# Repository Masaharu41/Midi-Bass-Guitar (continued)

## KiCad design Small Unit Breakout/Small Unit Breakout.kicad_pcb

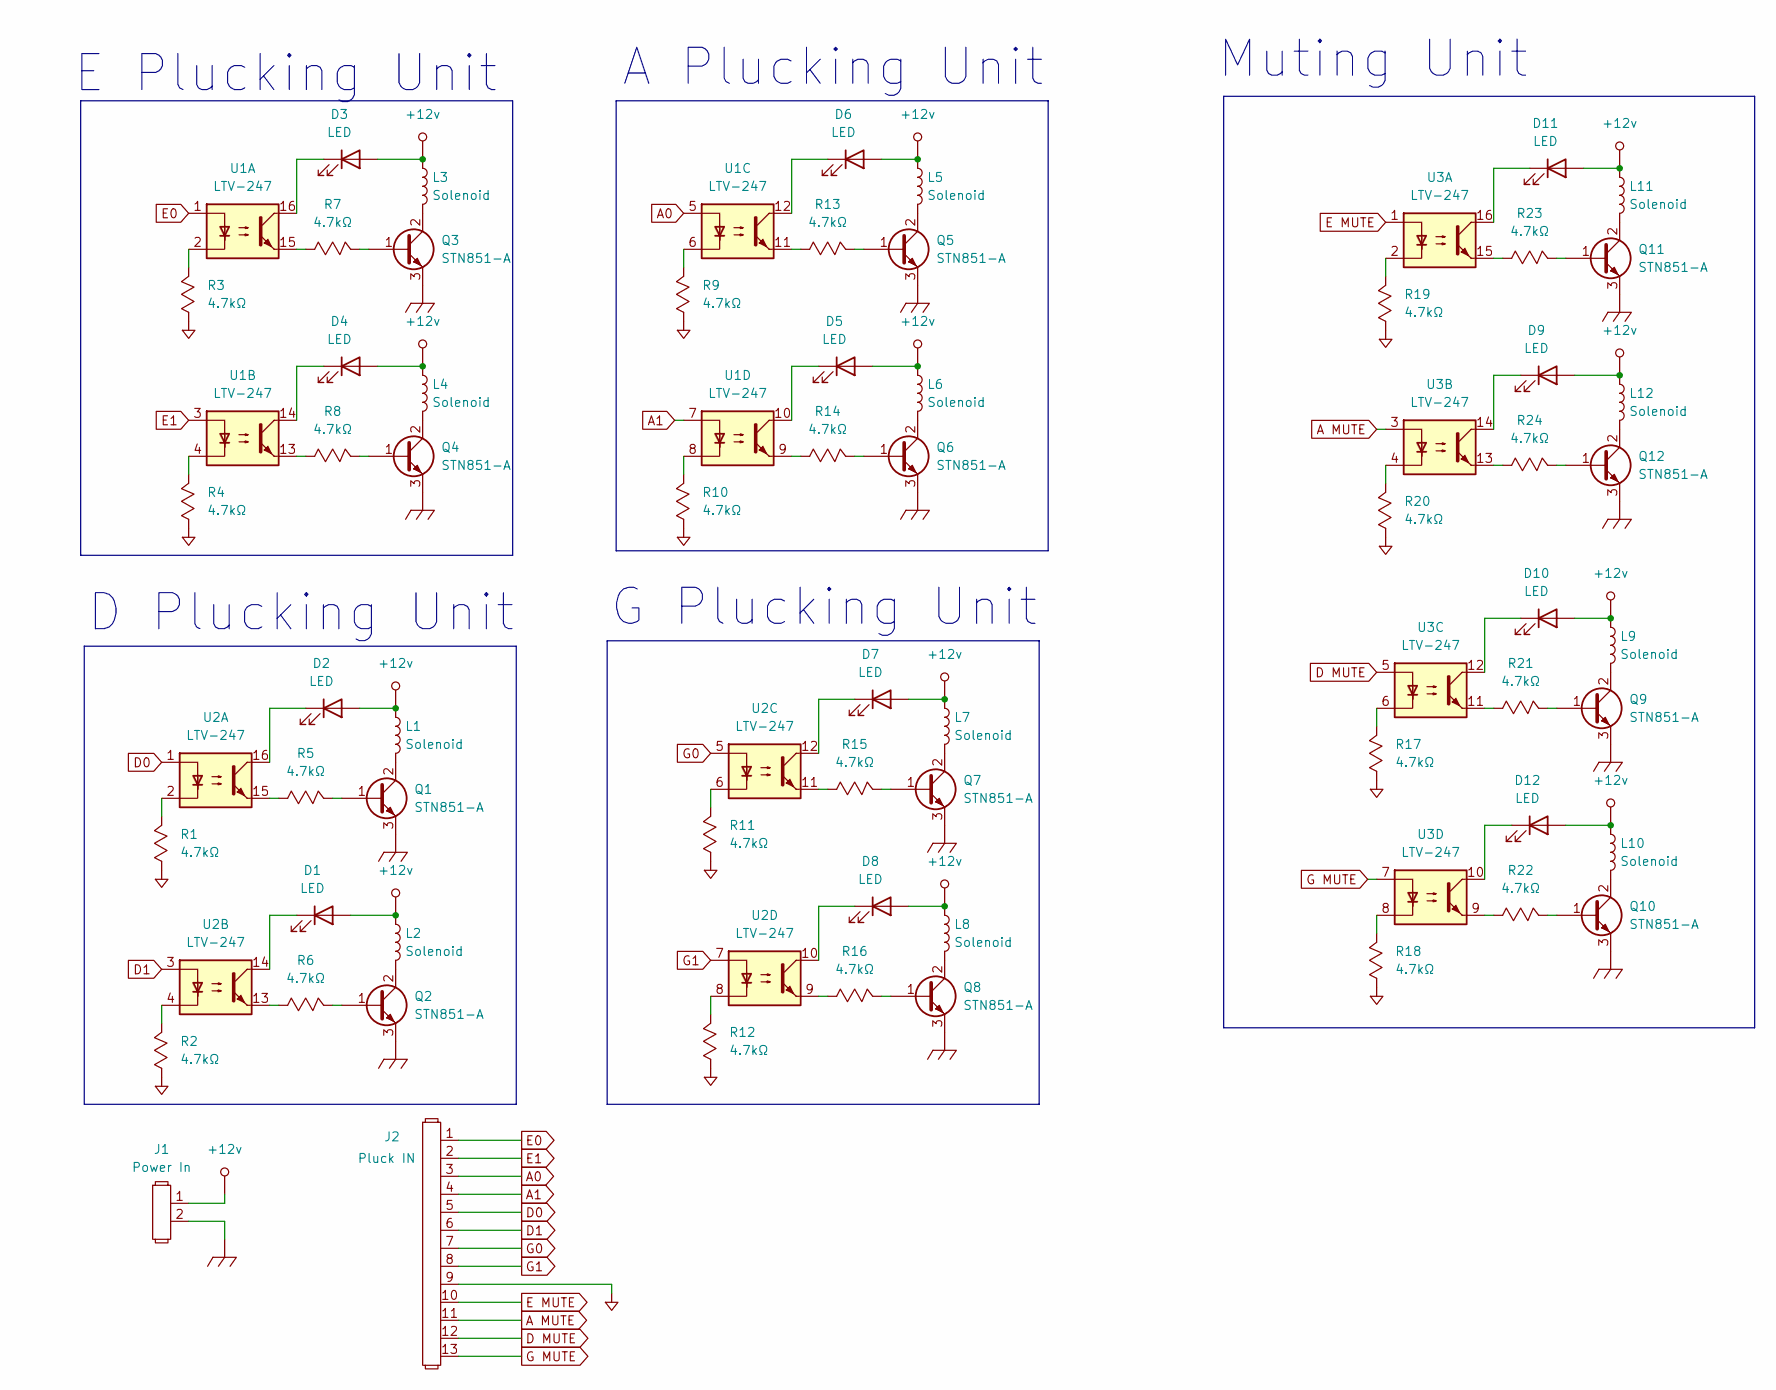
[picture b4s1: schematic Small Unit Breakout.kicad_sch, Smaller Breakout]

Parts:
D1, D2, D3, D4, D5, D6, D7, D8, D9, D10, D11, D12: LED; LED_0805_2012Metric_Pad1.15x1.40mm_HandSolder
J1: Power In; Two_Pin_Screw_Terminal
J2: Pluck IN; PinHeader_1x13_P2.54mm_Vertical
L1, L2, L3, L4, L5, L6, L7, L8, L9, L10, L11, L12: Solenoid; PinHeader_1x02_P2.54mm_Vertical
Q1, Q2, Q3, Q4, Q5, Q6, Q7, Q8, Q9, Q10, Q11, Q12: STN851-A; SOT-223-3_TabPin2
R1, R2, R3, R4, R5, R6, R7, R8, R9, R10, R11, R12, R13, R14, R15, R16, R17, R18, R19, R20, R21, R22, R23, R24: 4.7kΩ; R_0805_2012Metric_Pad1.20x1.40mm_HandSolder
U1, U2, U3: LTV-247; SOP-16_4.4x10.4mm_P1.27mm

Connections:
+12v: D1.2 (A), D2.2 (A), D3.2 (A), D4.2 (A), D5.2 (A), D6.2 (A), D7.2 (A), D8.2 (A), D9.2 (A), D10.2 (A), D11.2 (A), D12.2 (A), J1.1, L1.1, L2.1, L3.1, L4.1, L5.1, L6.1, L7.1, L8.1, L9.1, L10.1, L11.1, L12.1; also elsewhere on the board
A0: J2.3, U1.5
A1: J2.4, U1.7
A MUTE: J2.11, U3.3
Chassis_GND: J1.2, Q1.3 (E), Q2.3 (E), Q3.3 (E), Q4.3 (E), Q5.3 (E), Q6.3 (E), Q7.3 (E), Q8.3 (E), Q9.3 (E), Q10.3 (E), Q11.3 (E), Q12.3 (E); also elsewhere on the board
D0: J2.5, U2.1
D1: J2.6, U2.3
D MUTE: J2.12, U3.5
E0: J2.1, U1.1
E1: J2.2, U1.3
E MUTE: J2.10, U3.1
G0: J2.7, U2.5
G1: J2.8, U2.7
G MUTE: J2.13, U3.7
GND: J2.9, R1.1, R2.1, R3.1, R4.1, R9.1, R10.1, R11.1, R12.1, R17.1, R18.1, R19.1, R20.1
unnamed: D1.1 (K), U2.14
unnamed: D2.1 (K), U2.16
unnamed: D3.1 (K), U1.16
unnamed: D4.1 (K), U1.14
unnamed: D5.1 (K), U1.10
unnamed: D6.1 (K), U1.12
unnamed: D7.1 (K), U2.12
unnamed: D8.1 (K), U2.10
unnamed: D9.1 (K), U3.14
unnamed: D10.1 (K), U3.12
unnamed: D11.1 (K), U3.16
unnamed: D12.1 (K), U3.10
unnamed: Q1.1 (B), R5.2
unnamed: L1.2, Q1.2 (C)
unnamed: Q2.1 (B), R6.2
unnamed: L2.2, Q2.2 (C)
unnamed: Q3.1 (B), R7.2
unnamed: L3.2, Q3.2 (C)
unnamed: Q4.1 (B), R8.2
unnamed: L4.2, Q4.2 (C)
unnamed: Q5.1 (B), R13.2
unnamed: L5.2, Q5.2 (C)
unnamed: Q6.1 (B), R14.2
unnamed: L6.2, Q6.2 (C)
unnamed: Q7.1 (B), R15.2
unnamed: L7.2, Q7.2 (C)
unnamed: Q8.1 (B), R16.2
unnamed: L8.2, Q8.2 (C)
unnamed: Q9.1 (B), R21.2
unnamed: L9.2, Q9.2 (C)
unnamed: Q10.1 (B), R22.2
unnamed: L10.2, Q10.2 (C)
unnamed: Q11.1 (B), R23.2
unnamed: L11.2, Q11.2 (C)
unnamed: Q12.1 (B), R24.2
unnamed: L12.2, Q12.2 (C)
unnamed: R1.2, U2.2
unnamed: R2.2, U2.4
unnamed: R3.2, U1.2
unnamed: R4.2, U1.4
unnamed: R5.1, U2.15
unnamed: R6.1, U2.13
unnamed: R7.1, U1.15
unnamed: R8.1, U1.13
unnamed: R9.2, U1.6
unnamed: R10.2, U1.8
unnamed: R11.2, U2.6
unnamed: R12.2, U2.8
unnamed: R13.1, U1.11
unnamed: R14.1, U1.9
unnamed: R15.1, U2.11
unnamed: R16.1, U2.9
unnamed: R17.2, U3.6
unnamed: R18.2, U3.8
unnamed: R19.2, U3.2
unnamed: R20.2, U3.4
unnamed: R21.1, U3.11
unnamed: R22.1, U3.9
unnamed: R23.1, U3.15
unnamed: R24.1, U3.13

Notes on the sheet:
Muting Unit
G Plucking Unit
D Plucking Unit
E Plucking Unit
A Plucking Unit

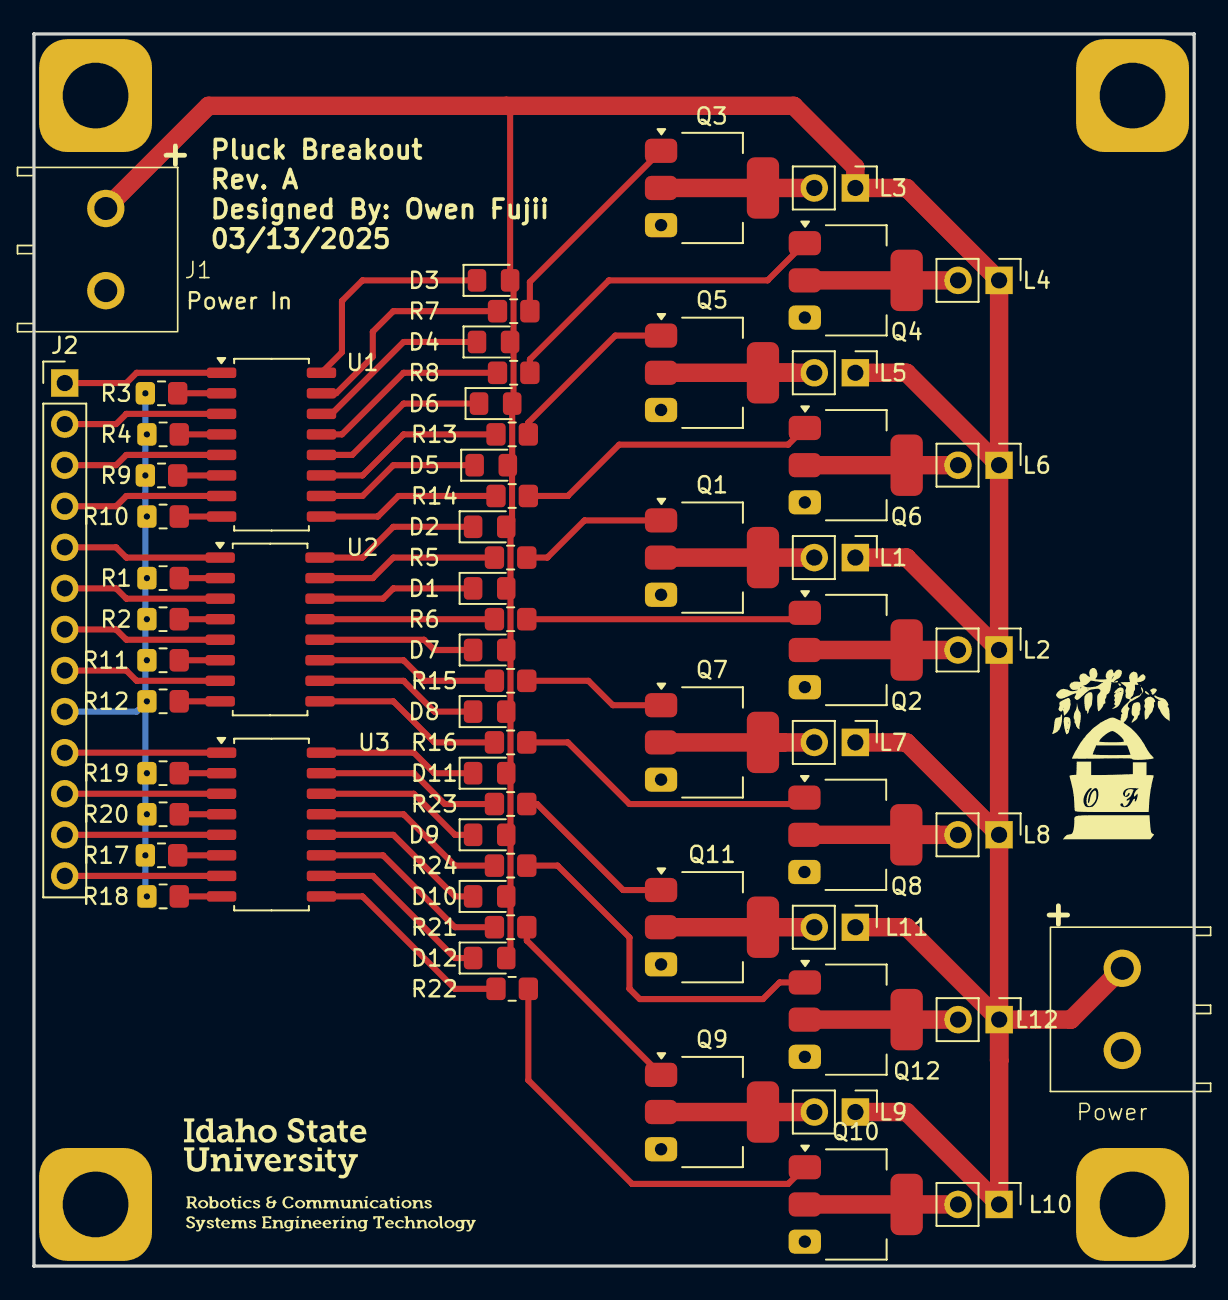
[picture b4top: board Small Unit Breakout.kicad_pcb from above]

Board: 2 copper layers, 71.8 x 76.2 mm, 66 parts (0 on the bottom side), 75 nets.

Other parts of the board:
Power: Two_Pin_Screw_Terminal

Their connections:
+12v: Power.2; also elsewhere on the board
Chassis_GND: Power.1; also elsewhere on the board

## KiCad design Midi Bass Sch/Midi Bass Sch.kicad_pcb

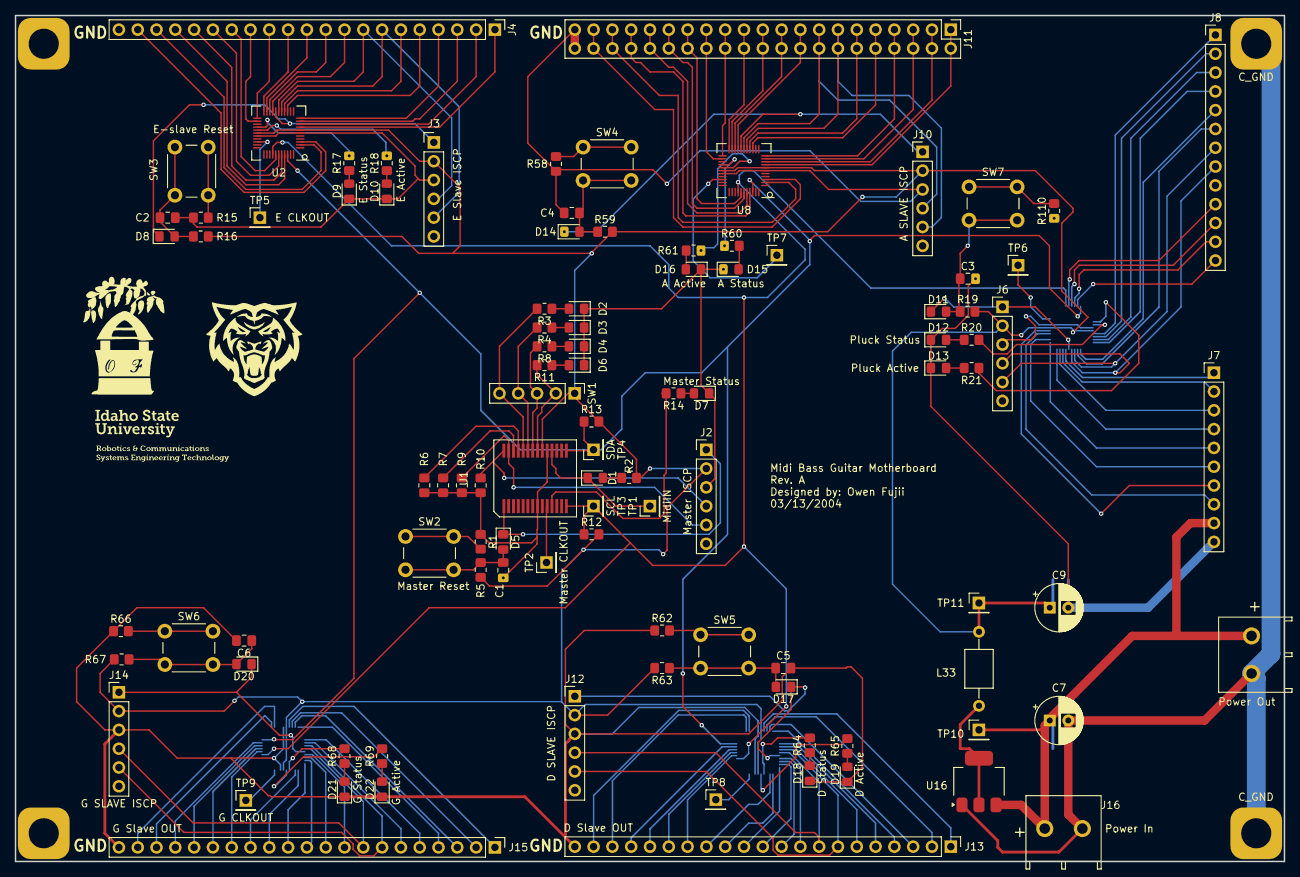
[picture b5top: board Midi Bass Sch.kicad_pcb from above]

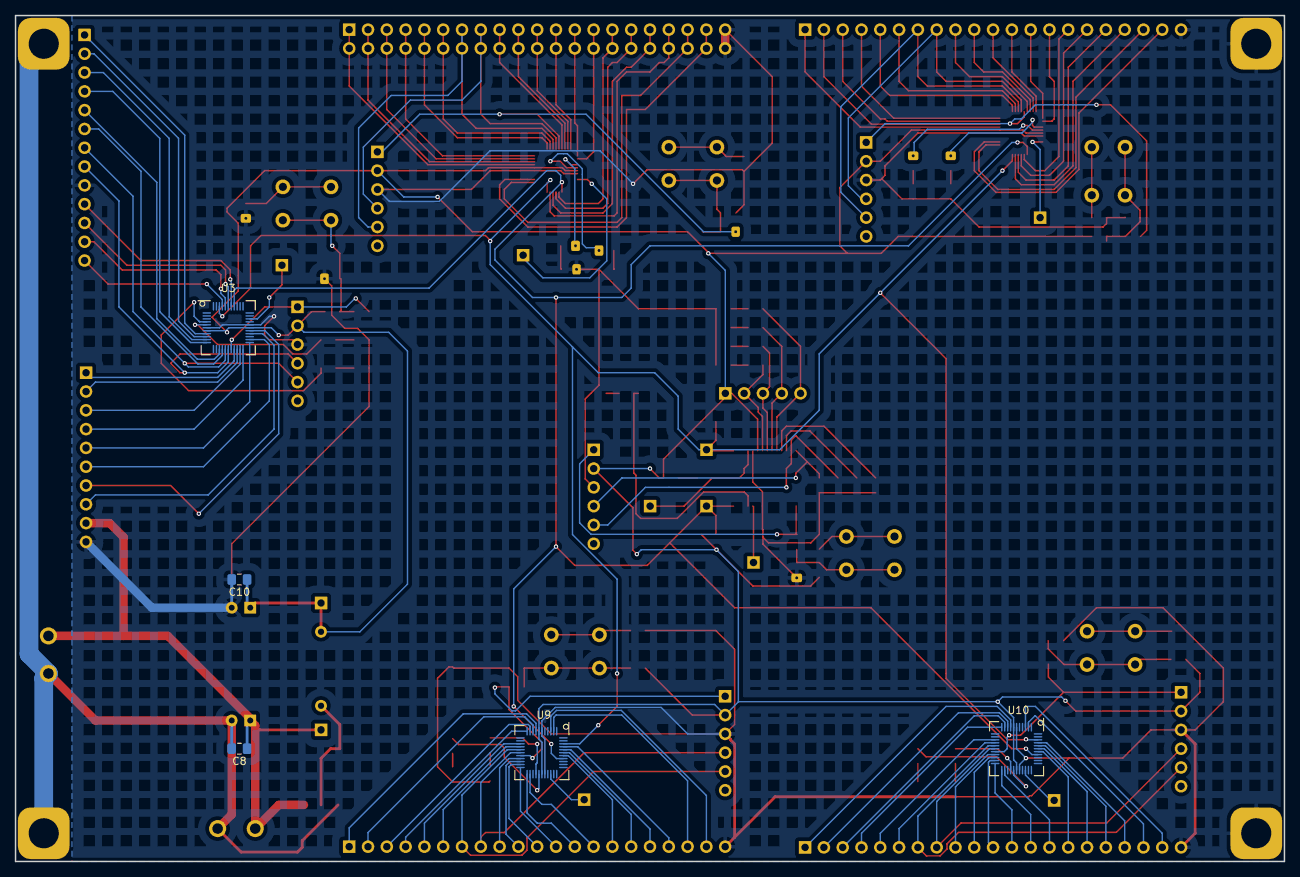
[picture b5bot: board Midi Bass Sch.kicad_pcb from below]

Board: 2 copper layers, 171.5 x 114.3 mm, 106 parts (5 on the bottom side), 167 nets.

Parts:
C1, C2, C3, C4, C5, C6: 10uF; C_0805_2012Metric_Pad1.18x1.45mm_HandSolder
C7, C9: 100uF; CP_Radial_D6.3mm_P2.50mm
C8, C10: 0.1uF; C_0805_2012Metric_Pad1.18x1.45mm_HandSolder
D1: LED; D_0805_2012Metric_Pad1.15x1.40mm_HandSolder
D2: 8; D_0805_2012Metric_Pad1.15x1.40mm_HandSolder
D3: 4; D_0805_2012Metric_Pad1.15x1.40mm_HandSolder
D4: 2; D_0805_2012Metric_Pad1.15x1.40mm_HandSolder
D5, D8, D11, D14, D17, D20: 4148; D_0805_2012Metric_Pad1.15x1.40mm_HandSolder
D6: 1; D_0805_2012Metric_Pad1.15x1.40mm_HandSolder
D7: Master Status; D_0805_2012Metric_Pad1.15x1.40mm_HandSolder
D9: E Status; D_0805_2012Metric_Pad1.15x1.40mm_HandSolder
D10: E Active; D_0805_2012Metric_Pad1.15x1.40mm_HandSolder
D12: Pluck Status; D_0805_2012Metric_Pad1.15x1.40mm_HandSolder
D13: Pluck Active; D_0805_2012Metric_Pad1.15x1.40mm_HandSolder
D15: A Status; D_0805_2012Metric_Pad1.15x1.40mm_HandSolder
D16: A Active; D_0805_2012Metric_Pad1.15x1.40mm_HandSolder
D18: D Status; D_0805_2012Metric_Pad1.15x1.40mm_HandSolder
D19: D Active; D_0805_2012Metric_Pad1.15x1.40mm_HandSolder
D21: G Status; D_0805_2012Metric_Pad1.15x1.40mm_HandSolder
D22: G Active; D_0805_2012Metric_Pad1.15x1.40mm_HandSolder
J2: Master ISCP; PinHeader_1x06_P2.54mm_Vertical
J3: E SLAVE ISCP; PinHeader_1x06_P2.54mm_Vertical
J4: E Slave Out; PinHeader_1x21_P2.54mm_Vertical
J6: Pluck ISCP; PinHeader_1x06_P2.54mm_Vertical
J7: Pick Unit; PinHeader_1x10_P2.54mm_Vertical
J8: Pluck Out; PinHeader_1x13_P2.54mm_Vertical
J10: A SLAVE ISCP; PinHeader_1x06_P2.54mm_Vertical
J11: A Slave OUT; PinHeader_2x21_P2.54mm_Vertical
J12: D SLAVE ISCP; PinHeader_1x06_P2.54mm_Vertical
J13: D Slave OUT; PinHeader_1x21_P2.54mm_Vertical
J14: G SLAVE ISCP; PinHeader_1x06_P2.54mm_Vertical
J15: G Slave OUT; PinHeader_1x21_P2.54mm_Vertical
J16: Power In; Two_Pin_Screw_Terminal
L33: 10uH; L_Axial_L5.0mm_D3.6mm_P10.00mm_Horizontal_Murata_BL01RN1A2A2
Power Out: Two_Pin_Screw_Terminal
R1, R15, R58, R62, R66, R110: 10Ω; R_0805_2012Metric_Pad1.20x1.40mm_HandSolder
R2: 1kΩ; R_0805_2012Metric_Pad1.20x1.40mm_HandSolder
R3, R4, R8, R11, R14, R17, R18, R20, R21, R60, R61, R64, R65, R68, R69: 330Ω; R_0805_2012Metric_Pad1.20x1.40mm_HandSolder
R5, R6, R7, R9, R10, R16, R19, R59, R63, R67: 10kΩ; R_0805_2012Metric_Pad1.20x1.40mm_HandSolder
R12, R13: 2.2kΩ; R_0805_2012Metric_Pad1.20x1.40mm_HandSolder
SW1: PinHeader_1x05_P2.54mm_Vertical
SW2: Master Reset; SW_PUSH_6mm_H5mm
SW3: E-slave Reset; SW_PUSH_6mm_H5mm
SW4: A-slave Reset; SW_PUSH_6mm_H5mm
SW5: D-slave Reset; SW_PUSH_6mm_H5mm
SW6: G-slave Reset; SW_PUSH_6mm_H5mm
SW7: Pluck Reset; SW_PUSH_6mm_H5mm
TP1: MidiIN; PinHeader_1x01_P2.54mm_Vertical
TP2: Master CLKOUT; PinHeader_1x01_P2.54mm_Vertical
TP3: SCL; PinHeader_1x01_P2.54mm_Vertical
TP4: SDA; PinHeader_1x01_P2.54mm_Vertical
TP5: E CLKOUT; PinHeader_1x01_P2.54mm_Vertical
TP6: PLUCK CLKOUT; PinHeader_1x01_P2.54mm_Vertical
TP7: A CLKOUT; PinHeader_1x01_P2.54mm_Vertical
TP8: D CLKOUT; PinHeader_1x01_P2.54mm_Vertical
TP9: G CLKOUT; PinHeader_1x01_P2.54mm_Vertical
TP10: P-IN; PinHeader_1x01_P2.54mm_Vertical
TP11: 5v; PinHeader_1x01_P2.54mm_Vertical
U1: PIC16F1788; SSOP-28
U2, U3, U8, U9, U10: PIC16F1789; TQFN-44_7x7_Pitch0.4mm
U16: LM1117MP-1.8; SOT-223-3_TabPin2

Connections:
1: R11.2, SW1.2 (1), U1.21 (INT/AN12/RB0)
2: R8.2, SW1.3 (2), U1.22 (P1C/AN10/RB1)
4: R4.2, SW1.4, U1.23 (P1B/AN8/RB2)
8: R3.2, SW1.5 (8), U1.24 (PGM/C12IN2-/AN8/RB3)
+5v: C9.1, C10.1, J2.2, J3.2, J6.2, J10.2, J12.2, J14.2, L33.2, R2.2, R5.2, R12.2, R13.2, R16.2, R19.2, R59.2, R63.2, R67.2, SW1.1 (Com), TP11.1, U1.20 (VDD), U2.7 (Vdd), U2.28 (Vdd), U3.7 (Vdd), U3.28 (Vdd), U8.7 (Vdd), U8.28 (Vdd), U9.7 (Vdd), U9.28 (Vdd), U10.7 (Vdd), U10.28 (Vdd)
+12v: C7.1, C8.1, J7.9, J16.1, Power Out.2, TP10.1, U16.3 (VI)
/String Strike Slave/A0: J8.3, U3.10 (RB2/AN8/OPA2IN-/DAC3OUT1)
/String Strike Slave/A1: J8.4, U3.11 (RB3/AN9/CXNI2-/CCP2)
/String Strike Slave/A MUTE: J8.11, U3.39 (RD1/CxIN4-/OPA3OUT)
/String Strike Slave/D0: J8.5, U3.14 (RB4/AN11/C3IN1+)
/String Strike Slave/D1: J8.6, U3.15 (RB5/AN13/C4IN2-/CCP3)
/String Strike Slave/D MUTE: J8.12, U3.40 (RD2/OPA3IN-/DAC4OUT1)
/String Strike Slave/E0: J8.1, U3.8 (RB0/AN12/CCP1/C2IN1+)
/String Strike Slave/E1: J8.2, U3.9 (RB1/AN10/CxIN3-/OPA2OUT)
/String Strike Slave/E MUTE: J8.10, U3.38 (RD0/OPA3IN+)
/String Strike Slave/G MUTE: J8.13, U3.41 (RD3/PSMC4A)
A1: J4.5, U2.14 (RB4/AN11/C3IN1+)
A2: J4.17, U2.40 (RD2/OPA3IN-/DAC4OUT1)
A#1: J4.6, U2.15 (RB5/AN13/C4IN2-/CCP3)
A#2: J4.18, U2.41 (RD3/PSMC4A)
B1: J3.5, J4.7, U2.16 (RB6/C4IN1+/ICSPCLK)
B2: J4.19, U2.2 (RD4/PSM3F)
C2: J3.4, J4.8, U2.17 (RB7/DACxOUT2-/ICSPDAT)
C3: J4.20, U2.3 (RD5/PSMC3E)
C#2: J4.9, U2.19 (RA0/AN0/CxIN0-)
D2: J4.10, U2.20 (RA1/AN1/CxIN1-/OPA1OUT)
D#2: J4.11, U2.21 (RA2/AN2/CxIN0+/DAC1OUT1)
E2: J4.12, U2.22 (RA3/AN3/VREF+/C1IN1+)
Earth_GND: C7.2, C8.2, J16.2, Power Out.1, U16.1 (GND)
F1: J4.1, U2.8 (RB0/AN12/CCP1/C2IN1+)
F2: J4.13, U2.23 (RA4/C1OUT/OPA1IN+/T0CKI)
F#1: J4.2, U2.9 (RB1/AN10/CxIN3-/OPA2OUT)
F#2: J4.14, U2.24 (RA5/AN4/C2OUT/OPA1IN+)
G1: J4.3, U2.10 (RB2/AN8/OPA2IN-/DAC3OUT1)
G2: J4.15, U2.38 (RD0/OPA3IN+)
G#1: J4.4, U2.11 (RB3/AN9/CXNI2-/CCP2)
G#2: J4.16, U2.39 (RD1/CxIN4-/OPA3OUT)
GND: C1.2, C2.2, C3.2, C4.2, C5.2, C6.2, C9.2, C10.2, D2.1 (K), D3.1 (K), D4.1 (K), D6.1 (K), D7.1 (K), D9.1 (K), D10.1 (K), D12.1 (K), D13.1 (K), D15.1 (K), D16.1 (K), D18.1 (K), D19.1 (K), D21.1 (K), D22.1 (K), J2.3, J3.3, J4.21, J6.3, J7.10, J8.9, J10.3, J11.21, J12.3, J13.21, J14.3, J15.21, R1.1, R6.1, R7.1, R9.1, R10.1, R15.1, R58.1, R62.1, R66.1, R110.1, U1.8 (VSS), U1.19 (VSS), U2.6 (Vss), U2.29 (Vss), U3.6 (Vss), U3.29 (Vss), U8.6 (Vss), U8.29 (Vss), U9.6 (Vss), U9.29 (Vss), U10.6 (Vss), U10.29 (Vss)
I2Cclk: R12.1, TP3.1, U1.14 (RC3/SCK/SCL), U2.37 (RC3/SCL/SCK/PSMC1D), U3.37 (RC3/SCL/SCK/PSMC1D), U8.37 (RC3/SCL/SCK/PSMC1D), U9.37 (RC3/SCL/SCK/PSMC1D), U10.37 (RC3/SCL/SCK/PSMC1D)
I2Cdat: R13.1, TP4.1, U1.15 (RC4/SDI/SDA), U2.42 (RC4/SDI/SDA/PSMC1E), U3.42 (RC4/SDI/SDA/PSMC1E), U8.42 (RC4/SDI/SDA/PSMC1E), U9.42 (RC4/SDI/SDA/PSMC1E), U10.42 (RC4/SDI/SDA/PSMC1E)
MSCLR A: D14.1, J10.1, U8.18 (Vpp/~MCLR/RE3)
MSCLR D: D17.1, J12.1, U9.18 (Vpp/~MCLR/RE3)
MSCLR E: D8.1, J3.1, U2.18 (Vpp/~MCLR/RE3)
MSCLR G: D20.1, J14.1, U10.18 (Vpp/~MCLR/RE3)
MSCLR P: D11.1, J6.1, U3.18 (Vpp/~MCLR/RE3)
unnamed: C1.1, D5.2, R5.1, SW2.2
unnamed: C2.1, D8.2, R16.1, SW3.2
unnamed: C3.1, D11.2, R19.1, SW7.2
unnamed: C4.1, D14.2, R59.1, SW4.2
unnamed: C5.1, D17.2, R63.1, SW5.2
unnamed: C6.1, D20.2, R67.1, SW6.2
unnamed: D1.2 (A), R2.1
unnamed: D1.1 (K), TP1.1, U1.18 (RC7/RX/DT)
unnamed: D2.2 (A), R3.1
unnamed: D3.2 (A), R4.1
unnamed: D4.2 (A), R8.1
unnamed: D6.2 (A), R11.1
unnamed: D7.2 (A), R14.1
unnamed: D9.2 (A), R17.1
unnamed: D10.2 (A), R18.1
unnamed: D12.2 (A), R20.1
unnamed: D13.2 (A), R21.2
unnamed: D15.2 (A), R60.1
unnamed: D16.2 (A), R61.1
unnamed: D18.2 (A), R64.1
unnamed: D19.2 (A), R65.1
unnamed: D21.2 (A), R68.1
unnamed: D22.2 (A), R69.1
unnamed: R1.2, SW2.1
unnamed: R15.2, SW3.1
unnamed: R58.2, SW4.1
unnamed: R62.2, SW5.1
unnamed: R66.2, SW6.1
unnamed: R110.2, SW7.1
unnamed: TP2.1, U1.10 (CLKOUT/OSC2/RA6)
unnamed: R6.2, U1.25 (P1D/AN11/RB4)
unnamed: R14.2, U1.11 (RC0/T1OSO/T1CK1)
unnamed: D5.1, J2.1, U1.1 (RE3/~MCLR/Vpp)
unnamed: R7.2, U1.26 (~T1G/AN13/RB5)
unnamed: TP5.1, U2.31 (RA6/C2OUT/CLKOUT)
unnamed: R17.2, U2.26 (RE1/AN6/PSMC3B)
unnamed: R18.2, U2.27 (RE2/AN7/PSMC3A)
unnamed: J7.1, U3.19 (RA0/AN0/CxIN0-)
unnamed: J7.2, U3.20 (RA1/AN1/CxIN1-/OPA1OUT)
unnamed: J7.3, U3.21 (RA2/AN2/CxIN0+/DAC1OUT1)
unnamed: J7.4, U3.22 (RA3/AN3/VREF+/C1IN1+)
unnamed: J7.5, U3.23 (RA4/C1OUT/OPA1IN+/T0CKI)
unnamed: J7.6, U3.24 (RA5/AN4/C2OUT/OPA1IN+)
unnamed: TP6.1, U3.31 (RA6/C2OUT/CLKOUT)
unnamed: R21.1, U3.4 (RD6/PSMC3D)
unnamed: R20.2, U3.5 (RD7/C4OUT/PSMC3C)
unnamed: J7.8, U3.26 (RE1/AN6/PSMC3B)
unnamed: J7.7, U3.27 (RE2/AN7/PSMC3A)
unnamed: J11.9, U8.19 (RA0/AN0/CxIN0-)
unnamed: J11.10, U8.20 (RA1/AN1/CxIN1-/OPA1OUT)
unnamed: J11.11, U8.21 (RA2/AN2/CxIN0+/DAC1OUT1)
unnamed: J11.12, U8.22 (RA3/AN3/VREF+/C1IN1+)
unnamed: J11.13, U8.23 (RA4/C1OUT/OPA1IN+/T0CKI)
unnamed: J11.14, U8.24 (RA5/AN4/C2OUT/OPA1IN+)
unnamed: TP7.1, U8.31 (RA6/C2OUT/CLKOUT)
unnamed: J11.1, U8.8 (RB0/AN12/CCP1/C2IN1+)
unnamed: J11.2, U8.9 (RB1/AN10/CxIN3-/OPA2OUT)
unnamed: J11.3, U8.10 (RB2/AN8/OPA2IN-/DAC3OUT1)
unnamed: J11.4, U8.11 (RB3/AN9/CXNI2-/CCP2)
unnamed: J11.5, U8.14 (RB4/AN11/C3IN1+)
unnamed: J11.6, U8.15 (RB5/AN13/C4IN2-/CCP3)
unnamed: J11.15, U8.38 (RD0/OPA3IN+)
unnamed: J11.16, U8.39 (RD1/CxIN4-/OPA3OUT)
unnamed: J11.17, U8.40 (RD2/OPA3IN-/DAC4OUT1)
unnamed: J11.18, U8.41 (RD3/PSMC4A)
unnamed: J11.19, U8.2 (RD4/PSM3F)
unnamed: J11.20, U8.3 (RD5/PSMC3E)
unnamed: R60.2, U8.26 (RE1/AN6/PSMC3B)
unnamed: R61.2, U8.27 (RE2/AN7/PSMC3A)
unnamed: J13.9, U9.19 (RA0/AN0/CxIN0-)
unnamed: J13.10, U9.20 (RA1/AN1/CxIN1-/OPA1OUT)
unnamed: J13.11, U9.21 (RA2/AN2/CxIN0+/DAC1OUT1)
unnamed: J13.12, U9.22 (RA3/AN3/VREF+/C1IN1+)
unnamed: J13.13, U9.23 (RA4/C1OUT/OPA1IN+/T0CKI)
unnamed: J13.14, U9.24 (RA5/AN4/C2OUT/OPA1IN+)
unnamed: TP8.1, U9.31 (RA6/C2OUT/CLKOUT)
unnamed: J13.1, U9.8 (RB0/AN12/CCP1/C2IN1+)
unnamed: J13.2, U9.9 (RB1/AN10/CxIN3-/OPA2OUT)
unnamed: J13.3, U9.10 (RB2/AN8/OPA2IN-/DAC3OUT1)
unnamed: J13.4, U9.11 (RB3/AN9/CXNI2-/CCP2)
unnamed: J13.5, U9.14 (RB4/AN11/C3IN1+)
unnamed: J13.6, U9.15 (RB5/AN13/C4IN2-/CCP3)
unnamed: J13.15, U9.38 (RD0/OPA3IN+)
unnamed: J13.16, U9.39 (RD1/CxIN4-/OPA3OUT)
unnamed: J13.17, U9.40 (RD2/OPA3IN-/DAC4OUT1)
unnamed: J13.18, U9.41 (RD3/PSMC4A)
unnamed: J13.19, U9.2 (RD4/PSM3F)
unnamed: J13.20, U9.3 (RD5/PSMC3E)
unnamed: R64.2, U9.26 (RE1/AN6/PSMC3B)
unnamed: R65.2, U9.27 (RE2/AN7/PSMC3A)
unnamed: J15.9, U10.19 (RA0/AN0/CxIN0-)
unnamed: J15.10, U10.20 (RA1/AN1/CxIN1-/OPA1OUT)
unnamed: J15.11, U10.21 (RA2/AN2/CxIN0+/DAC1OUT1)
unnamed: J15.12, U10.22 (RA3/AN3/VREF+/C1IN1+)
unnamed: J15.13, U10.23 (RA4/C1OUT/OPA1IN+/T0CKI)
unnamed: J15.14, U10.24 (RA5/AN4/C2OUT/OPA1IN+)
unnamed: TP9.1, U10.31 (RA6/C2OUT/CLKOUT)
unnamed: J15.1, U10.8 (RB0/AN12/CCP1/C2IN1+)
unnamed: J15.2, U10.9 (RB1/AN10/CxIN3-/OPA2OUT)
unnamed: J15.3, U10.10 (RB2/AN8/OPA2IN-/DAC3OUT1)
unnamed: J15.4, U10.11 (RB3/AN9/CXNI2-/CCP2)
unnamed: J15.5, U10.14 (RB4/AN11/C3IN1+)
unnamed: J15.6, U10.15 (RB5/AN13/C4IN2-/CCP3)
unnamed: J15.15, U10.38 (RD0/OPA3IN+)
unnamed: J15.16, U10.39 (RD1/CxIN4-/OPA3OUT)
unnamed: J15.17, U10.40 (RD2/OPA3IN-/DAC4OUT1)
unnamed: J15.18, U10.41 (RD3/PSMC4A)
unnamed: J15.19, U10.2 (RD4/PSM3F)
unnamed: J15.20, U10.3 (RD5/PSMC3E)
unnamed: R68.2, U10.26 (RE1/AN6/PSMC3B)
unnamed: R69.2, U10.27 (RE2/AN7/PSMC3A)
unnamed: L33.1, U16.2 (VO)
RB6 A: J10.5, J11.7, U8.16 (RB6/C4IN1+/ICSPCLK)
RB6 D: J12.5, J13.7, U9.16 (RB6/C4IN1+/ICSPCLK)
RB6 G: J14.5, J15.7, U10.16 (RB6/C4IN1+/ICSPCLK)
RB6 P: J6.5, J8.7, U3.16 (RB6/C4IN1+/ICSPCLK)
RB6M: J2.5, R9.2, U1.27 (ICSPCLK/RB6)
RB7 A: J10.4, J11.8, U8.17 (RB7/DACxOUT2-/ICSPDAT)
RB7 D: J12.4, J13.8, U9.17 (RB7/DACxOUT2-/ICSPDAT)
RB7 G: J14.4, J15.8, U10.17 (RB7/DACxOUT2-/ICSPDAT)
RB7 P: J6.4, J8.8, U3.17 (RB7/DACxOUT2-/ICSPDAT)
RB7M: J2.4, R10.2, U1.28 (ICSPDAT/RB7)

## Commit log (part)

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2024-11-05 readded file
2024-11-05 added schematic files
2024-11-05 Added Master Assembly
2024-11-05 added include for I2C write
2024-11-05 modified I2C write to be usable with two byte transmit
2024-11-05 adding uart recieve and clean building all files currently successful
2024-11-05 finished basic master communication protocol
2024-11-05 updated hours
2024-11-06 added comments to MidiMaster detailing data
2024-11-06 added include files for storing working and eeprom
2024-11-06 updated schematic
2024-11-06 cleared interrupts for I2C writes
2024-11-06 added slave for string control
2024-11-06 added asm for dummy pluck slave
2024-11-06 Fixed issue with 32mhz oscillator setup
2024-11-07 updated hours sheet to current
2024-11-07 updated I2C include to assembler preferred labels
2024-11-07 added new comments and working on I2C issue
2024-11-07 added registers for notes on the slave
2024-11-07 working on setting output to ports
2024-11-07 added the basic model for bass body
2024-11-08 updated bass body and hours
2024-11-09 finished adding all Eslave output selects
2024-11-09 updated registers for output operation
2024-11-09 working on making note play work
2024-11-11 updated comments
2024-11-11 updated body to include neck and pickup cutouts
2024-11-11 started basic pickguard solid part
2024-11-11 added simplified bridge models
2024-11-11 added basic bridge saddle solid model
2024-11-12 added positions of frets
2024-11-12 modified schematic to include seperate sheets for master and slaves
2024-11-13 working on updating slave to select note slave
2024-11-13 added note limit calculations and working on select
2024-11-13 finishing higher note eval and adding string limit eval
2024-11-13 updated header of master
2024-11-14 finished rough structure for pitch up selection
2024-11-14 finished rough structure for lower notes
2024-11-14 updated note down to use prior note
2024-11-14 added dummy slave for A string
2024-11-14 added dummy slave for D string
2024-11-14 added dummy slave for G string
2024-11-14 updated appearance in main assembly
2024-11-14 resolved hole misalignment of pickguard and body
2024-11-15 added simple solenoid body cad model
2024-11-15 added basic cad model for solenoid plunger
2024-11-15 updated solenoid plunger
2024-11-15 updating plucking slave for outputs
2024-11-15 working on pluck slave need to analyze trigger circuitry
2024-11-18 finished framework for alternating enable for all strings
2024-11-18 implemented clear function for plucking units
2024-11-18 began implementing I2C stop condition properly at this point I2C is broken
2024-11-19 added file for report
2024-11-19 began working on background information
2024-11-19 resolved I2C issues with Master and Slaves
2024-11-19 fixed alternating function for each string in pluck slave
2024-11-19 reduced time of pulse
2024-11-19 fixed issue with hitting notes on rest
2024-11-19 updated table of values to include hex for E string
2024-11-19 created functional block diagram for project
2024-11-19 updated schematic to include solenoids for pluck slave
2024-11-19 changed solenoid to a seperate sheet to include all plucking units
2024-11-20 updated schematic to include test points for pics
2024-11-20 updated schematic to include all slaves
2024-11-20 implementing catches for out of bounds notes
2024-11-20 reworking down note algorithm
2024-11-20 updated notes sheet
2024-11-20 master now verifies note on via 9 eval
2024-11-20 rolling E slave back to a simpler setup system to control string is being changed to a gantry system
2024-11-20 Added stepper controller to E slave
2024-11-21 updated e slave added solenoid for slave added reset button
2024-11-21 implimented basic stepper output step clock
2024-11-21 added stepper drive to E slave Testing is preliminary and not how it will be fully used
2024-11-21 added nested loops to respect the value of each bit in each byte
2024-11-21 began adding stepper location calculation into program
2024-11-21 finished first rev of stepper clock section Will now work on demo of stepper operation
2024-11-21 removed GPRs for notes, moving to table style
2024-11-22 updated report to include proprosed problem
2024-11-22 added flowchart for basic master program flow
2024-11-22 added flowchart for math section of master program
2024-11-22 added stepper calculation to main function
2024-11-22 I2C broken as of now
2024-11-22 rolled master program back to resolve I2C issues
2024-11-22 working on issues with I2C
2024-11-22 Rolled Master back to older version Will move to use I2C for confirmation
2024-11-22 reverting E slave to main Steppper motor idea ditched Reverting Back to Mass Solenoid system
2024-11-23 updated master schematic and block diagram updated hours as well added block diagram to report
2024-11-23 updated slave to 1789 to reflect new design updated 1789 to reflect thin flat pack
2024-11-23 added schematic page for solenoid array for E-slave
2024-11-23 updated number tables to include hex for all values
2024-11-24 updated solenoid array to use opto isolation
2024-11-24 added opto isolation to plucking solenoids
2024-11-24 working on system overview of report
2024-11-29 added note table and bitmap to report
2024-11-29 began adding section for string slave in report
2024-11-29 added solenoid array for the A slave
2024-11-29 added solenoid array for the D slave
2024-11-29 added solenoid array for the G slave
2024-12-01 added footprints to kicad schematic still need footprint for din connector
2024-12-01 began working on pcb for project
2024-12-02 began adding mute application to plucking unit
2024-12-02 finished prelim code for mute implementation
2024-12-02 mute works as intended with pluck unit
2024-12-02 updated hours troubleshooting issues with e slave
2024-12-02 added stop interrupt detect for E slave
2024-12-02 removed un-used include
2024-12-02 fixed issues with eval on master
2024-12-03 began working on plucking section of report
2024-12-03 added plucking string flowchart
2024-12-03 updated schematic to reflect code
2024-12-03 began writing calibration procedure
2024-12-03 E slave private changed
2024-12-03 added drawing for p-bass neck
2024-12-04 updated pluck schematic
2024-12-04 added drawing for bridge saddle
2024-12-04 updated title block of bass body drawing
2024-12-04 added drawing for pickguard
2024-12-04 added image folder added screenshot for full cad assembly
2024-12-04 added drawing for solenoid firing pin
2024-12-04 added pdf versions of all drawing sheets
2024-12-04 added waveform files and demo video
2024-12-04 working on finishing calibration section added image for hex switch
2024-12-05 finished expanding serial section
2024-12-05 began adding troubleshooting portion of report
2024-12-06 added flowchart for serial
2024-12-06 added flowchart for plucking unit added images of flowcharts
2024-12-06 modified flowcharts to use different end figure
2024-12-06 added schematic page for power
2024-12-06 working on troubleshooting section of report
2024-12-09 updated plucking schematic to label line
2024-12-09 finished troubleshooting section
2024-12-09 added labeled breadboard images
2024-12-09 corrected video name spelling
2024-12-09 updated flowchart for string slave
2024-12-09 moved report to LFS support
2024-12-09 finished conclusion
2024-12-09 finished recommendations
2024-12-10 updated bill of materials
2024-12-10 added slide show
2024-12-10 restructured slide show video broke presentation
2024-12-10 added flowcharts to presentation:
2024-12-10 finished BOM
2024-12-10 updated BOM to include labor
2024-12-10 changed transistor for schematic
2024-12-10 added mechanical drawings to report
2024-12-10 began getting images for schematic appendix
2024-12-10 fixed images
2024-12-10 added schematic to appendix
2024-12-10 updated presentation with serial commands also added command section to MIDI spreadsheet
2024-12-11 presentation good to roll
2024-12-11 finished report
2024-12-11 added borders to tables
2025-01-09 began working on pcb layout deleted extra schematics for solenoid break out board
2025-01-09 added traces for D processor began Pluck processor
2025-03-10 added seperate schematic for solenoid breakout
2025-03-11 finished rev A pcb for breakout:
2025-03-12 working in finishing Rev A pcb for motherboard
2025-03-13 added profile for extrusion
2025-03-14 updated motherboard pcb
2025-03-14 Working on first stages of CAD integration
2025-03-14 added angled bracket for extrusions
2025-03-14 added new hours tracking sheet for new semester
2025-03-14 began adding proposed frame to main assembly
2025-03-15 added cross bar and defined main assembly
2025-03-17 added D and G strings
2025-03-17 Extended Cage Length
2025-03-17 creating prelim plucking unit
2025-03-18 changed bar and brace updated hours
2025-03-18 created mount for solenoids
2025-03-18 added pickup slot to pickguard
2025-03-18 added E and A strings to assem updated daily hours
2025-03-19 added pin for small solenoid
2025-03-19 Added bracket to mount smaller solenoids
2025-03-20 Created mounting brackets for plucking solenoids E and D Updated hours
2025-03-22 added new part for A mounting
2025-03-22 near complete with initial mechanical drafts
2025-04-01 removed old code in E slave updated for multibyte recieve
2025-04-01 added first set of evals for new fret module
2025-04-01 currently revising solenoid breakout to match new design
2025-04-02 revised schematic for breakout updating PCB to match
2025-04-03 finished rev B pcb for solenoid breakout
2025-04-03 removed sheets of master schematic to match new design
2025-04-03 removed project folders for unused programs
2025-04-04 added rev b. zip files for new solenoid breakout
2025-04-04 added poweramp schematic
2025-04-05 new serial protocol for master implemented
2025-04-07 add ignore file
2025-04-07 remove duplicate add
2025-04-08 updated attributes
2025-04-08 added gitignore
2025-04-08 removed .x files
2025-04-08 readded gitignore
2025-04-08 added hours log and cleaned main asm for slave program
2025-04-08 tried opening kicad files but my local kicad is not up to date
2025-04-09 created test midi song for slave a, and addedd zach christensen's I2C protocol to help I2C troubleshooting
2025-04-15 updated and comments in some programs
2025-04-16 updated fret bar model to be through hole
2025-04-17 fret slave program v1 + updated hours
2025-04-22 integrated Justin's code into testing
2025-04-22 updated status and active
2025-04-23 updated comments on master working on verifying fret slave
2025-04-24 added new include file for converter
2025-04-24 added second stage of new eval method
2025-04-24 removed gerbers for small breakout
2025-04-24 updated main flowchart to match new design
2025-04-25 functional test verified for hex to one converter
2025-04-26 majority of midi recieved results in valid move waiting on other micro processor to fully test
2025-04-29 updated neck support brace to fit
2025-04-29 added fret bars for 2nd and 3rd frets
2025-04-30 renamed Midi bass sch to Motherboard Sch
2025-04-30 updated flowcharts and names
2025-04-30 adde more solenoids to main assembly
2025-05-01 designed new bars and added stls updated pluck unit to match new solenoids
2025-05-01 added new bracket for muting solenoids
2025-05-02 added kicad main build for motherboard
2025-05-02 added new models for electonics case :
2025-05-02 added stls for higher even frets
2025-05-04 designed new casing for breakout as well as prelim mounting solution for din rail
2025-05-04 began to update hours to current
2025-05-06 added new drawings for neck support
2025-05-06 added drawing for solenoid mount for 2020 rails
2025-05-06 added drawing sheet for top bracket
2025-05-06 added drawing for 4N solenoid
2025-05-06 added comments to pin blocks
2025-05-06 added drawing for short extrusion pdfs for both 2020 extrusions added
2025-05-06 moved drawing sheets and added sheet for 2020 long and lower bracket also added stl for din rail mounts
2025-05-06 updating for merge
2025-05-07 updated hours, created new 'main' branch
2025-05-07 finished hours
2025-05-07 added new models for muting unit to fit proper
2025-05-07 added flowchart for mechanical troubleshooting
2025-05-07 added images for individual schematic pages for motherboard
2025-05-07 added single pages for breakout
